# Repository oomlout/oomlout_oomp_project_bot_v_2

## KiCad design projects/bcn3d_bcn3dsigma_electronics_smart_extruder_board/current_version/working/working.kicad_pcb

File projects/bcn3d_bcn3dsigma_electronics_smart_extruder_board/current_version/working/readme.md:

# bcn3dsigma_electronics
 
## summary 
* id: bcn3d_bcn3dsigma_electronics_smart_extruder_board
* user: bcn3d
* name: bcn3dsigma_electronics
* board: smart_extruder_board
* repo: https://github.com/BCN3D/BCN3DSigma-Electronics

* src_file_repo_sch: 
* src_file_repo_sch_link: https://github.com/BCN3D/BCN3DSigma-Electronics/tree/master/
* full details link: https://github.com/oomlout/oomlout_oomp_project_bot_v_2/tree/main/projects/bcn3d_bcn3dsigma_electronics_smart_extruder_board/current_version/working  

## schematic  
  
[schematic (pdf)](working_schematic.pdf) 

## pcb  

[board (pdf)](working.pdf)  

## working_bom
| Id | Designator | Footprint | Quantity | Designation | Supplier and ref |  | None | 
| --- | --- | --- | --- | --- | --- | --- | --- | 
| 1 | @HOLE0,@HOLE1 |  | 2 |  |  |  | [''] | 
| 2 | C2,C1 | C0603K | 2 | 100n |  |  | [''] | 
| 3 | CFAN0,LFAN0,ENDSTOP0 | JST-2-SMD | 3 |  |  |  | [''] | 
| 4 | R8,R2 | R0603 | 2 | 10k |  |  | [''] | 
| 5 | R6,L1,R4 | R0603 | 3 | 1k |  |  | [''] | 
| 6 | R5 | R0603 | 1 | 200k |  |  | [''] | 
| 7 | U2 | SOT23-3 | 1 | LM3480IM4 |  |  | [''] | 
| 8 | R1 | R1210 | 1 | 100 |  |  | [''] | 
| 9 | U$1,U$2,U$3 | FIDUCIAL_1MM | 3 | FIDUCIAL |  |  | [''] | 
| 10 | U3 | MSOP8 | 1 | LM392MMSOP8 |  |  | [''] | 
| 11 | CN1 | JST_PA_04 | 1 |  |  |  | [''] | 
| 12 | D1 | POWERDI323 | 1 | PD3S160 |  |  | [''] | 
| 13 | Q2 | SOT323 | 1 | MOSFET-NSOT323 |  |  | [''] | 
| 14 | Q1 | SOT323-BEC | 1 | BC807W |  |  | [''] | 
| 15 | R3 | R0603 | 1 | 5k23 |  |  | [''] | 
| 16 | C3 | C0805 | 1 | 330n |  |  | [''] | 
| 17 | VERT_FFC1 | 68612014422 | 1 | 68612014422 |  |  | [''] | 
| 18 | R7 | R0603 | 1 | 22.6K |  |  | [''] | 
| 19 | GND0,THERM0,CFAN-0,UNK5V0,UNK24V0,CFAN+0 | B1,27 | 6 | TPB1,27 |  |  | [''] | 
| 20 | U$5 | OSHW-LOGO-S | 1 |  |  |  | [''] | 
| 21 | U$6 | FCIM_LOGO | 1 |  |  |  | [''] | 

## bom_schematic
| Ref | Qnty | Value | Cmp name | Footprint | Description | Vendor | DNP | 
| --- | --- | --- | --- | --- | --- | --- | --- | 
| C1, C2 | 2 | 100n | C-EUC0603K | working:C0603K |  |  |  | 
| C3 | 1 | 330n | C-EUC0805 | working:C0805 |  |  |  | 
| CFAN0 | 1 | JST_2MM_MALE | JST_2MM_MALE | working:JST-2-SMD |  |  |  | 
| CFAN+0 | 1 | TPB1,27 | TPB1,27 | working:B1,27 |  |  |  | 
| CFAN-0 | 1 | TPB1,27 | TPB1,27 | working:B1,27 |  |  |  | 
| CN1 | 1 | JST_4PINPA | JST_4PINPA | working:JST_PA_04 |  |  |  | 
| D1 | 1 | PD3S160 | PD3S160 | working:POWERDI323 |  |  |  | 
| ENDSTOP0 | 1 | JST_2MM_MALE | JST_2MM_MALE | working:JST-2-SMD |  |  |  | 
| GND0 | 1 | TPB1,27 | TPB1,27 | working:B1,27 |  |  |  | 
| L1 | 1 | 1k | R-US_R0603 | working:R0603 |  |  |  | 
| LFAN0 | 1 | JST_2MM_MALE | JST_2MM_MALE | working:JST-2-SMD |  |  |  | 
| Q1 | 1 | BC807W | BC807W | working:SOT323-BEC |  |  |  | 
| Q2 | 1 | MOSFET-NSOT323 | MOSFET-NSOT323 | working:SOT323 |  |  |  | 
| R1 | 1 | 100 | R-US_R1210 | working:R1210 |  |  |  | 
| R2, R8 | 2 | 10k | R-US_R0603 | working:R0603 |  |  |  | 
| R3 | 1 | 5k23 | R-US_R0603 | working:R0603 |  |  |  | 
| R4, R6 | 2 | 1k | R-US_R0603 | working:R0603 |  |  |  | 
| R5 | 1 | 200k | R-US_R0603 | working:R0603 |  |  |  | 
| R7 | 1 | 22.6K | R-US_R0603 | working:R0603 |  |  |  | 
| THERM0 | 1 | TPB1,27 | TPB1,27 | working:B1,27 |  |  |  | 
| U2 | 1 | LM3480IM4 | LM3480IM4 | working:SOT23-3 |  |  |  | 
| U3 | 1 | LM392MMSOP8 | LM392MMSOP8 | working:MSOP8 |  |  |  | 
| U$1, U$2, U$3 | 3 | FIDUCIAL | FIDUCIAL | working:FIDUCIAL_1MM |  |  |  | 
| UNK5V0 | 1 | TPB1,27 | TPB1,27 | working:B1,27 |  |  |  | 
| UNK24V0 | 1 | TPB1,27 | TPB1,27 | working:B1,27 |  |  |  | 
| VERT_FFC1 | 1 | 68612014422 | 68612014422 | working:68612014422 |  |  |  |

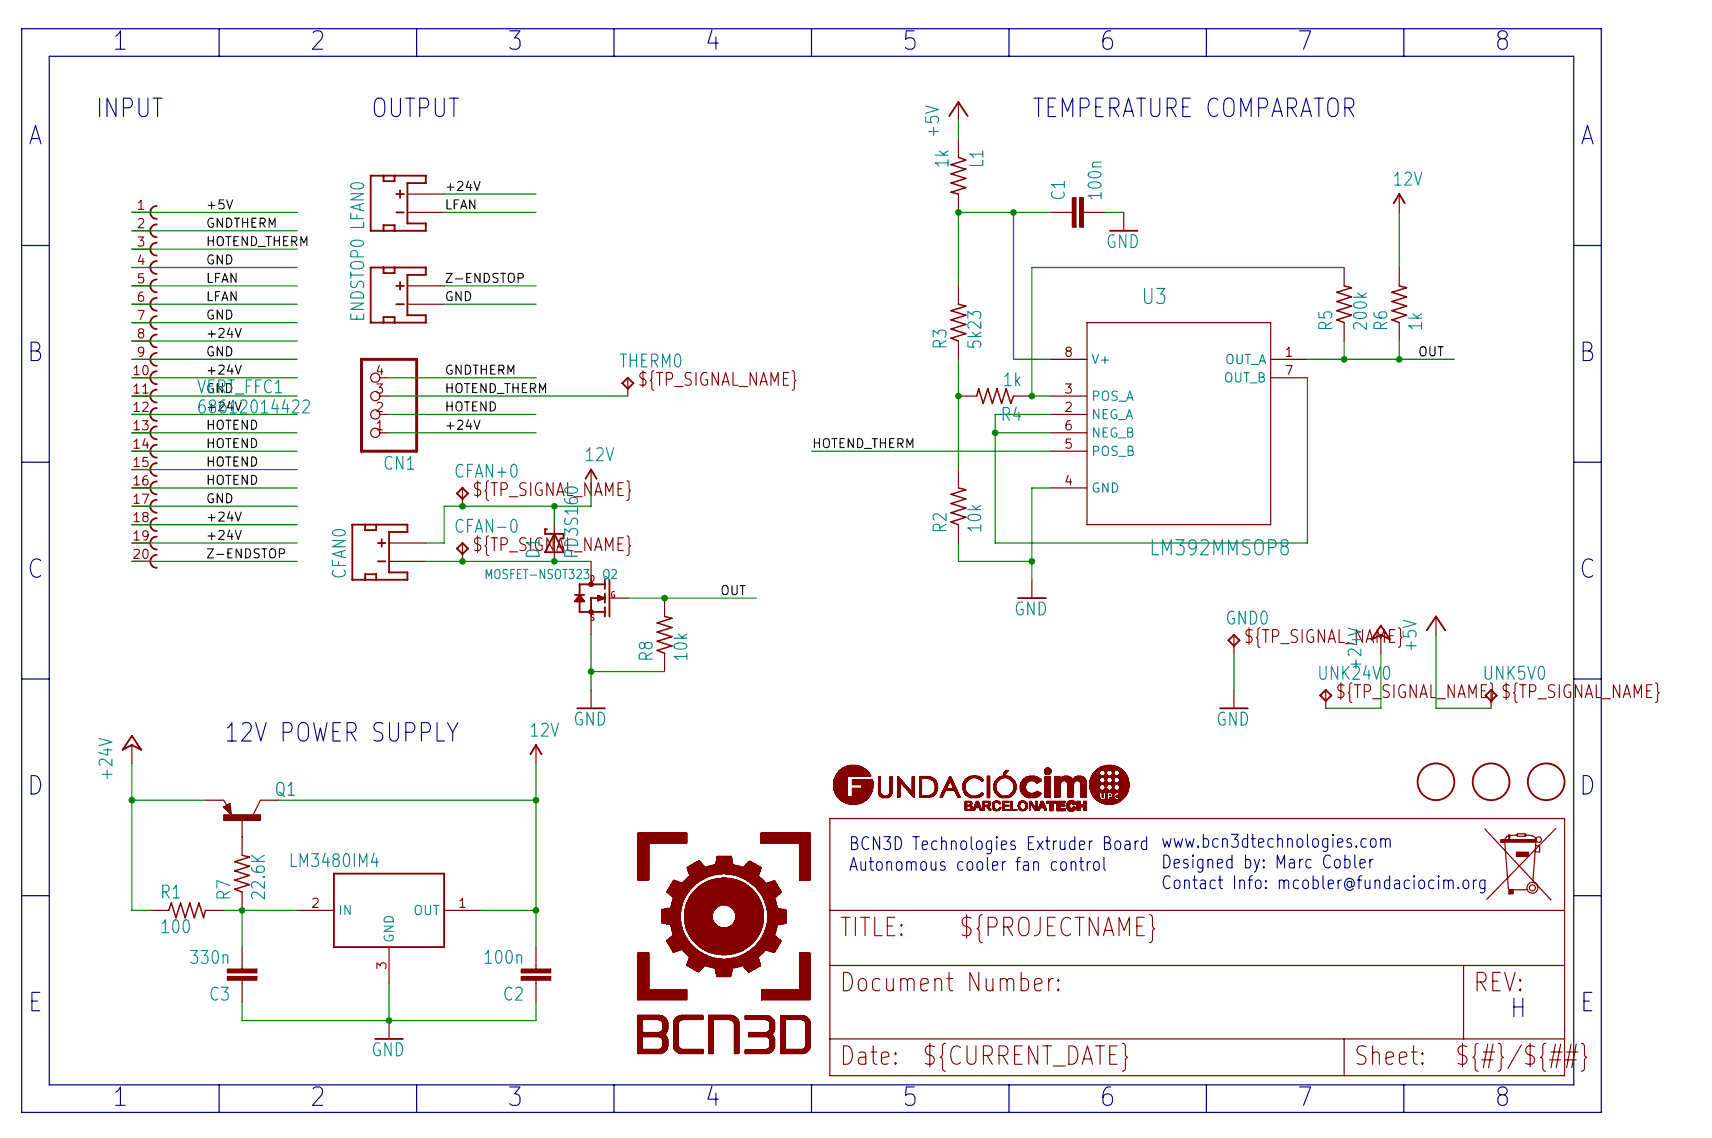
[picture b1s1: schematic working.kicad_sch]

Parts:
C1, C2: 100n; C0603K; MPN 06035C104KAT2A
C3: 330n; C0805; MPN GRM219R71H334KA88D
CFAN0: JST_2MM_MALE; JST-2-SMD; MPN S2B-PH-SM4-TB(LF)(SN)
CFAN+0: TPB1,27; B1,27
CFAN-0: TPB1,27; B1,27
CN1: JST_4PINPA; JST_PA_04; MPN SM04B-PASS-TBT(LF)(SN)
D1: PD3S160; POWERDI323; MPN PD3S160-7
ENDSTOP0: JST_2MM_MALE; JST-2-SMD; MPN S2B-PH-SM4-TB(LF)(SN)
GND0: TPB1,27; B1,27
L1: 1k; R0603; MPN MCMR06X1001FTL
LFAN0: JST_2MM_MALE; JST-2-SMD; MPN S2B-PH-SM4-TB(LF)(SN)
Q1: BC807W; SOT323-BEC; MPN BC807W,115
Q2: MOSFET-NSOT323; SOT323; MPN PMF370XN,115
R1: 100; R1210; MPN MC0603SAF330JT5E
R2, R8: 10k; R0603; MPN MCMR06X1002FTL
R3: 5k23; R0603; MPN ERJ3EKF5231V
R4, R6: 1k; R0603; MPN MCMR06X1001FTL
R5: 200k; R0603; MPN ERJ3EKF2003V
R7: 22.6K; R0603; MPN MC0603SAF330JT5E
THERM0: TPB1,27; B1,27
U2: LM3480IM4; SOT23-3; MPN LM3480IM3-12/NOPB
U3: LM392MMSOP8; MSOP8
U$1, U$2, U$3: FIDUCIAL; FIDUCIAL_1MM
UNK5V0, UNK24V0: TPB1,27; B1,27
VERT_FFC1: 68612014422

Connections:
12V: C2.2, CFAN0.2 (+), CFAN+0.TP, D1.C, Q1.3 (C), R6.2, U2.1 (OUT)
+5V: L1.1, UNK5V0.TP, VERT_FFC1.1
+24V: CN1.1, LFAN0.2 (+), Q1.2 (E), R1.1, UNK24V0.TP, VERT_FFC1.8, VERT_FFC1.10, VERT_FFC1.12, VERT_FFC1.18, VERT_FFC1.19
DRAIN: CFAN0.1 (-), CFAN-0.TP, D1.A, Q2.3 (D)
GND: C1.2, C2.1, C3.1, ENDSTOP0.1 (-), GND0.TP, Q2.2 (S), R2.1, R8.1, U2.3 (GND), U3.4 (GND), VERT_FFC1.4, VERT_FFC1.7, VERT_FFC1.9, VERT_FFC1.11, VERT_FFC1.17
GNDTHERM: CN1.4, VERT_FFC1.2
HOTEND: CN1.2, VERT_FFC1.13, VERT_FFC1.14, VERT_FFC1.15, VERT_FFC1.16
HOTEND_THERM: CN1.3, THERM0.TP, U3.5 (POS_B), VERT_FFC1.3
IN: C3.2, R1.2, R7.1, U2.2 (IN)
LFAN: LFAN0.1 (-), VERT_FFC1.5, VERT_FFC1.6
unnamed: Q1.1 (B), R7.2
unnamed: C1.1, L1.2, R3.2, U3.8 (V+)
unnamed: U3.2 (NEG_A), U3.6 (NEG_B), U3.7 (OUT_B)
unnamed: R2.2, R3.1, R4.2
unnamed: R4.1, R5.2, U3.3 (POS_A)
OUT: Q2.1 (G), R5.1, R6.1, R8.2, U3.1 (OUT_A)
Z-ENDSTOP: ENDSTOP0.2 (+), VERT_FFC1.20

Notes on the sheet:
BCN3D Technologies Extruder Board Autonomous cooler fan control
12V POWER SUPPLY
INPUT
www.bcn3dtechnologies.com Designed by: Marc Cobler Contact Info: mcobler@fundaciocim.org
OUTPUT
TEMPERATURE COMPARATOR

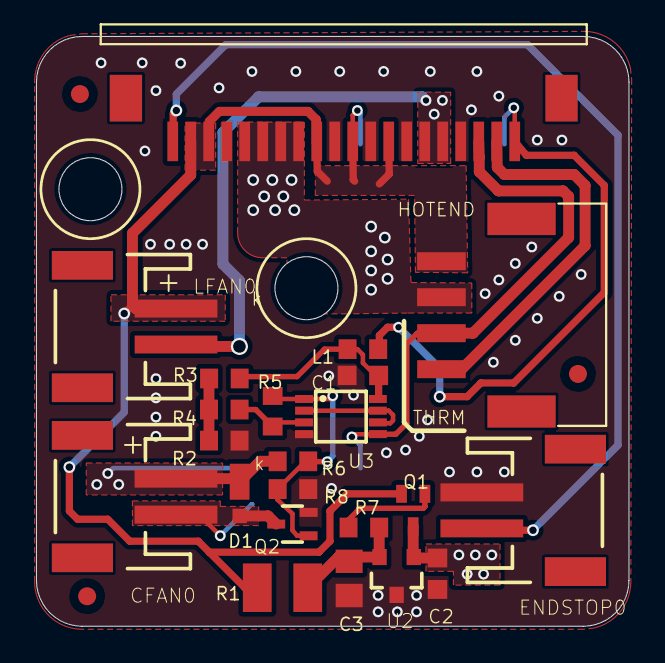
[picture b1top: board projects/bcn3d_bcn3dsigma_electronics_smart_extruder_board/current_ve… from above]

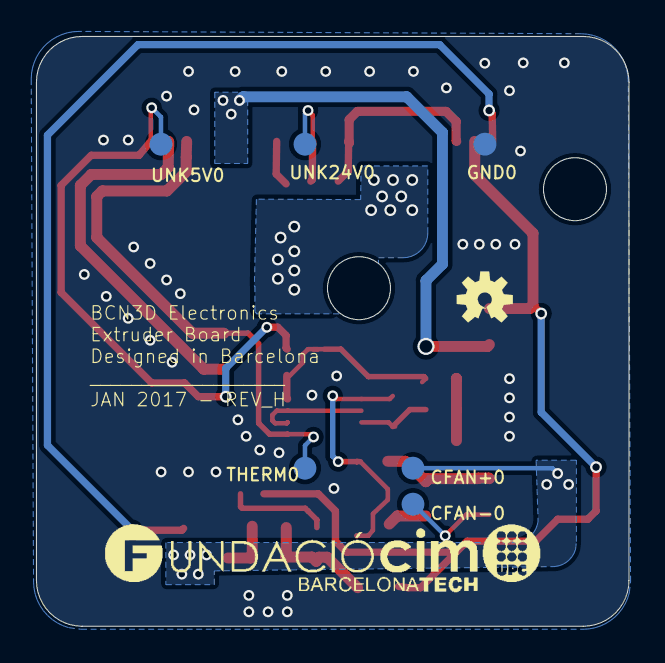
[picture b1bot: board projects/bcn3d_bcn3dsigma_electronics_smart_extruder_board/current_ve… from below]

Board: 2 copper layers, 32.9 x 32.8 mm, 35 parts (8 on the bottom side), 17 nets.

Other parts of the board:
@HOLE0, @HOLE1: (no value)
U$5: OSHW-LOGO-S
U$6: FCIM_LOGO

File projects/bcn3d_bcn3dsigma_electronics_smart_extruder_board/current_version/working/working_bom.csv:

"Id";"Designator";"Footprint";"Quantity";"Designation";"Supplier and ref";
1;"@HOLE0,@HOLE1";"";2;"";;;
2;"C2,C1";"C0603K";2;"100n";;;
3;"CFAN0,LFAN0,ENDSTOP0";"JST-2-SMD";3;"";;;
4;"R8,R2";"R0603";2;"10k";;;
5;"R6,L1,R4";"R0603";3;"1k";;;
6;"R5";"R0603";1;"200k";;;
7;"U2";"SOT23-3";1;"LM3480IM4";;;
8;"R1";"R1210";1;"100";;;
9;"U$1,U$2,U$3";"FIDUCIAL_1MM";3;"FIDUCIAL";;;
10;"U3";"MSOP8";1;"LM392MMSOP8";;;
11;"CN1";"JST_PA_04";1;"";;;
12;"D1";"POWERDI323";1;"PD3S160";;;
13;"Q2";"SOT323";1;"MOSFET-NSOT323";;;
14;"Q1";"SOT323-BEC";1;"BC807W";;;
15;"R3";"R0603";1;"5k23";;;
16;"C3";"C0805";1;"330n";;;
17;"VERT_FFC1";"68612014422";1;"68612014422";;;
18;"R7";"R0603";1;"22.6K";;;
19;"GND0,THERM0,CFAN-0,UNK5V0,UNK24V0,CFAN+0";"B1,27";6;"TPB1,27";;;
20;"U$5";"OSHW-LOGO-S";1;"";;;
21;"U$6";"FCIM_LOGO";1;"";;;

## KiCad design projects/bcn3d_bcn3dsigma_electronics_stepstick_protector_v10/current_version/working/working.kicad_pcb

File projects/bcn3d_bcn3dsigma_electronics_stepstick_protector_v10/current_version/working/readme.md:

# bcn3dsigma_electronics
 
## summary 
* id: bcn3d_bcn3dsigma_electronics_stepstick_protector_v10
* user: bcn3d
* name: bcn3dsigma_electronics
* board: stepstick_protector_v10
* repo: https://github.com/BCN3D/BCN3DSigma-Electronics

* src_file_repo_sch: 
* src_file_repo_sch_link: https://github.com/BCN3D/BCN3DSigma-Electronics/tree/master/
* full details link: https://github.com/oomlout/oomlout_oomp_project_bot_v_2/tree/main/projects/bcn3d_bcn3dsigma_electronics_stepstick_protector_v10/current_version/working  

## schematic  
  
[schematic (pdf)](working_schematic.pdf) 

## pcb  

[board (pdf)](working.pdf)  

## working_bom
| Id | Designator | Footprint | Quantity | Designation | Supplier and ref |  | None | 
| --- | --- | --- | --- | --- | --- | --- | --- | 
| 1 | C3 | C0402 | 1 | 470n/10V |  |  | [''] | 
| 2 | X1,X2 | PASSER_07MM | 2 | PASSER-07 |  |  | [''] | 
| 3 | C1,C7,C2,C6 | C0402 | 4 | 100n/50V |  |  | [''] | 
| 4 | C5 | C0402 | 1 | 22n/50V |  |  | [''] | 
| 5 | R2,R4 | M0805 | 2 | R0805/0R11 |  |  | [''] | 
| 6 | IC1 | QFN36-PAD | 1 | TMC2100-LA |  |  | [''] | 
| 7 | JP4,JP3,JP5 | 1X01 | 3 |  |  |  | [''] | 
| 8 | CFG5,CFG4 | JUMPER3-0201 | 2 | JUMPER3-0201 |  |  | [''] | 
| 9 | C8 | C0603 | 1 | 1u/50V |  |  | [''] | 
| 10 | R5 | C0402 | 1 | 20k |  |  | [''] | 
| 11 | C4 | C0402 | 1 | 4u7/10V |  |  | [''] | 
| 12 | JP1,JP2 | 1X08-S | 2 |  |  |  | [''] | 
| 13 | R1 | C0402 | 1 | 2R2 |  |  | [''] | 
| 14 | SPI0 | JUMPER2-0402_NC | 1 | JUMPER2-0402-NC |  |  | [''] | 
| 15 | R6 | POT_EVM3R | 1 | 20k |  |  | [''] | 
| 16 | LOGO2 | SPARK_TPLACE_M | 1 | LOGO-S_PLACE_M |  |  | [''] | 
| 17 | LOGO1 | OSHW_6X70 | 1 | OSHW_LOGOX0070 |  |  | [''] | 

## bom_schematic
| Ref | Qnty | Value | Cmp name | Footprint | Description | Vendor | DNP | 
| --- | --- | --- | --- | --- | --- | --- | --- | 
| C1, C2, C6, C7 | 4 | 100n/50V | CAPACITOR-0402 | working:C0402 |  |  |  | 
| C3 | 1 | 470n/10V | CAPACITOR-0402 | working:C0402 |  |  |  | 
| C4 | 1 | 4u7/10V | CAPACITOR-0402 | working:C0402 |  |  |  | 
| C5 | 1 | 22n/50V | CAPACITOR-0402 | working:C0402 |  |  |  | 
| C8 | 1 | 1u/50V | C-EUC0603 | working:C0603 |  |  |  | 
| CFG4, CFG5 | 2 | JUMPER3-0201 | JUMPER3-0201 | working:JUMPER3-0201 |  |  |  | 
| IC1 | 1 | TMC2100-LA | TMC2100-LA | working:QFN36-PAD |  |  |  | 
| JP1, JP2 | 2 | PINHD-1X08_2.54-S | PINHD-1X08_2.54-S | working:1X08-S |  |  |  | 
| JP3, JP4, JP5 | 3 | PINHD-1X1 | PINHD-1X1 | working:1X01 |  |  |  | 
| LOGO1 | 1 | OSHW_LOGOX0070 | OSHW_LOGOX0070 | working:OSHW_6X70 |  |  |  | 
| LOGO2 | 1 | LOGO-S_PLACE_M | LOGO-S_PLACE_M | working:SPARK_TPLACE_M |  |  |  | 
| R1 | 1 | 2R2 | RESISTOR-0402 | working:C0402 |  |  |  | 
| R2, R4 | 2 | R0805/0R11 | R-EU_M0805 | working:M0805 |  |  |  | 
| R5 | 1 | 20k | RESISTOR-0402 | working:C0402 |  |  |  | 
| R6 | 1 | 20k | POTEVM3R | working:POT_EVM3R |  |  |  | 
| SPI0 | 1 | JUMPER2-0402-NC | JUMPER2-0402-NC | working:JUMPER2-0402_NC |  |  |  | 
| X1, X2 | 2 | PASSER-07 | PASSER-07 | working:PASSER_07MM |  |  |  |

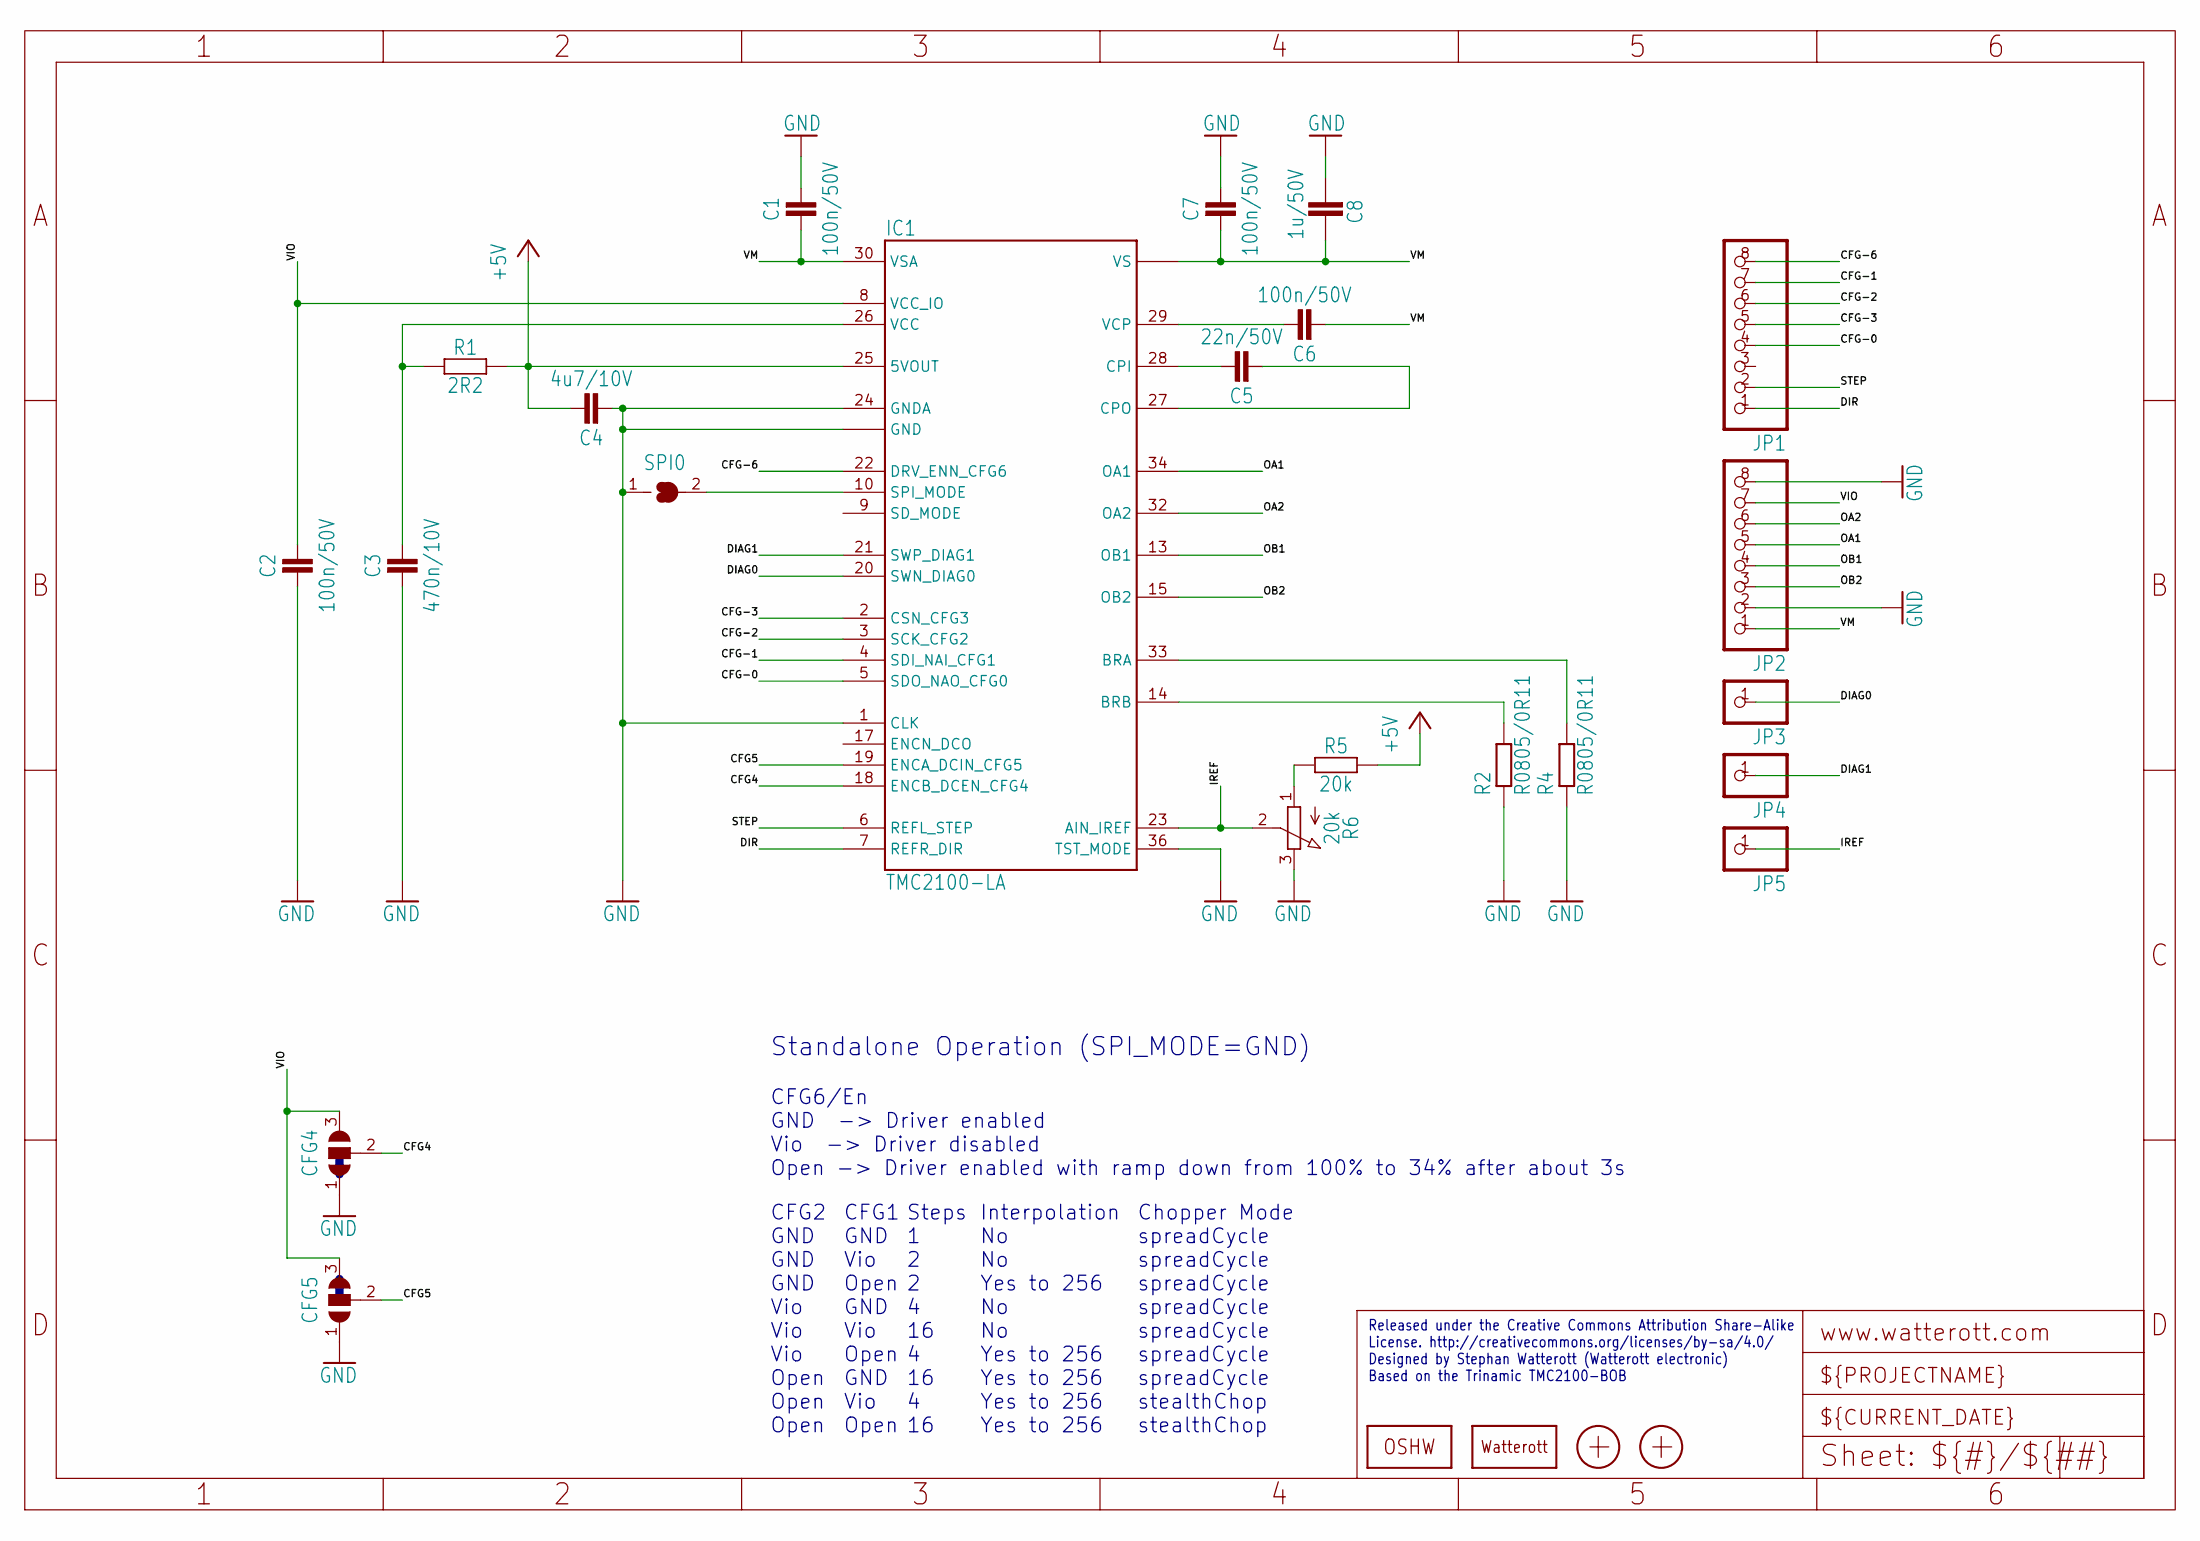
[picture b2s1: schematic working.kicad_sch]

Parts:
C1, C2, C6, C7: 100n/50V; C0402
C3: 470n/10V; C0402
C4: 4u7/10V; C0402
C5: 22n/50V; C0402
C8: 1u/50V; C0603
CFG4, CFG5: JUMPER3-0201
IC1: TMC2100-LA; QFN36-PAD
JP1, JP2: PINHD-1X08_2.54-S; 1X08-S
JP3, JP4, JP5: PINHD-1X1; 1X01
LOGO1: OSHW_LOGOX0070; OSHW_6X70
LOGO2: LOGO-S_PLACE_M; SPARK_TPLACE_M
R1: 2R2; C0402
R2, R4: R0805/0R11; M0805
R5: 20k; C0402
R6: 20k; POT_EVM3R
SPI0: JUMPER2-0402-NC; JUMPER2-0402_NC
X1, X2: PASSER-07; PASSER_07MM

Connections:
+5V: C4.2, IC1.25 (5VOUT), R1.2, R5.2
BRA: IC1.33 (BRA), R4.2
BRB: IC1.14 (BRB), R2.2
CFG4: CFG4.2, IC1.18 (ENCB_DCEN_CFG4)
CFG5: CFG5.2, IC1.19 (ENCA_DCIN_CFG5)
CFG-0: IC1.5 (SDO_NAO_CFG0), JP1.4
CFG-1: IC1.4 (SDI_NAI_CFG1), JP1.7
CFG-2: IC1.3 (SCK_CFG2), JP1.6
CFG-3: IC1.2 (CSN_CFG3), JP1.5
CFG-6: IC1.22 (DRV_ENN_CFG6), JP1.8
CPI: C5.2, IC1.28 (CPI)
CPO: C5.1, IC1.27 (CPO)
DIAG0: IC1.20 (SWN_DIAG0), JP3.1
DIAG1: IC1.21 (SWP_DIAG1), JP4.1
DIR: IC1.7 (REFR_DIR), JP1.1
GND: C1.2, C2.1, C3.1, C4.1, C7.2, C8.2, CFG4.1, CFG5.1, IC1.1 (CLK), IC1.11 (GND), IC1.12 (GND), IC1.24 (GNDA), IC1.35 (GND), IC1.36 (TST_MODE), IC1.TP (GND), JP2.2, JP2.8, R2.1, R4.1, R6.3 (E), SPI0.1
IREF: IC1.23 (AIN_IREF), JP5.1, R6.2 (S)
unnamed: IC1.10 (SPI_MODE), SPI0.2
OA1: IC1.34 (OA1), JP2.5
OA2: IC1.32 (OA2), JP2.6
OB1: IC1.13 (OB1), JP2.4
OB2: IC1.15 (OB2), JP2.3
STEP: IC1.6 (REFL_STEP), JP1.2
VCC: C3.2, IC1.26 (VCC), R1.1
VCP: C6.2, IC1.29 (VCP)
VIO: C2.2, CFG4.3, CFG5.3, IC1.8 (VCC_IO), JP2.7
VM: C1.1, C6.1, C7.1, C8.1, IC1.16 (VS), IC1.30 (VSA), IC1.31 (VS), JP2.1
VREF1: R5.1, R6.1 (A)

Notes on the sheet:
Standalone Operation (SPI_MODE=GND)
Released under the Creative Commons Attribution Share-Alike License. http://creativecommons.org/licenses/by-sa/4.0/ Designed by Stephan Watterott (Watterott electronic) Based on the Trinamic TMC2100-BOB
Interpolation No No Yes to 256 No No Yes to 256 Yes to 256 Yes to 256 Yes to 256
Steps 1 2 2 4 16 4 16 4 16
CFG6/En GND -> Driver enabled Vio -> Driver disabled Open -> Driver enabled with ramp down from 100% to 34% after about 3s
Chopper Mode spreadCycle spreadCycle spreadCycle spreadCycle spreadCycle spreadCycle spreadCycle stealthChop stealthChop
CFG1 GND Vio Open GND Vio Open GND Vio Open
CFG2 GND GND GND Vio Vio Vio Open Open Open

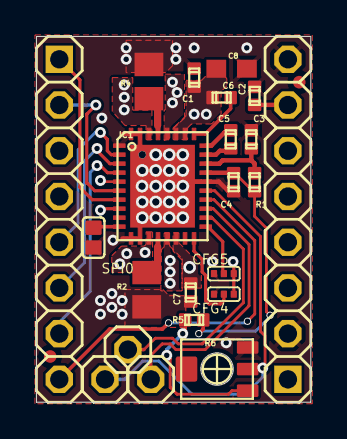
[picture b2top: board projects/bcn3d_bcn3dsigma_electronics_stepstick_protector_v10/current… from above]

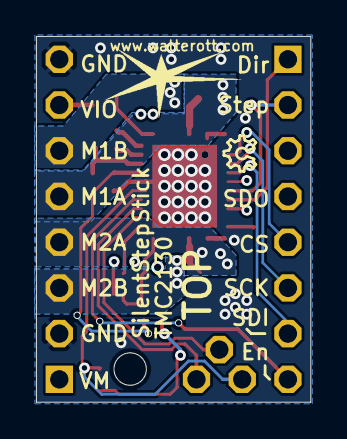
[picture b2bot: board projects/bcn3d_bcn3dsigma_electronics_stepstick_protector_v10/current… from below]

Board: 4 copper layers, 15.2 x 20.3 mm, 26 parts (2 on the bottom side), 28 nets.

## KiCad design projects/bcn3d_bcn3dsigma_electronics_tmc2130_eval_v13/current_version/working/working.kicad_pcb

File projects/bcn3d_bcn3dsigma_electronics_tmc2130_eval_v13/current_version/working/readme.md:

# bcn3dsigma_electronics
 
## summary 
* id: bcn3d_bcn3dsigma_electronics_tmc2130_eval_v13
* user: bcn3d
* name: bcn3dsigma_electronics
* board: tmc2130_eval_v13
* repo: https://github.com/BCN3D/BCN3DSigma-Electronics

* src_file_repo_sch: 
* src_file_repo_sch_link: https://github.com/BCN3D/BCN3DSigma-Electronics/tree/master/
* full details link: https://github.com/oomlout/oomlout_oomp_project_bot_v_2/tree/main/projects/bcn3d_bcn3dsigma_electronics_tmc2130_eval_v13/current_version/working  

## schematic  
  
[schematic (pdf)](working_schematic.pdf) 

## pcb  

[board (pdf)](working.pdf)  

## working_bom
| Id | Designator | Footprint | Quantity | Designation | Supplier and ref |  | None | 
| --- | --- | --- | --- | --- | --- | --- | --- | 
| 1 | PROBE_GND3,RSENSE_B0,PROBE_GND0,PROBE_GND2,PROBE_GND1,AIN_REF0,RSENSE_A0 | 1PIN_1ROW_THT | 7 | NOT ASSEMBLED |  |  | [''] | 
| 2 | TMC2130 | QFN36 | 1 | TMC2130_QFN36 |  |  | [''] | 
| 3 | JMP2 | EXTRA_TERMINAL | 1 | JUMPER_2.54MM BLACK ON X1 |  |  | [''] | 
| 4 | C7,C15,C5,C10 | C0603 | 4 | C0603/100nF/50V |  |  | [''] | 
| 5 | R11 | RCL_0603 | 1 | 15k/0603/1% |  |  | [''] | 
| 6 | INTERFACE_TO_UC/MC0 | FEMALE_HEADER_SMD_254_44_PIN_SHORTPADS_HOLES | 1 |  |  |  | [''] | 
| 7 | R10 | RCL_0603 | 1 | 10k/0603/1% |  |  | [''] | 
| 8 | R15,R14 | 0603 | 2 | 0603/1k/1% |  |  | [''] | 
| 9 | X1,REF2,X2 | 3PIN_1ROW_2,54_THT | 3 | MALE HEADER 2.54 |  |  | [''] | 
| 10 | TERM2 | EXTRA_TERMINAL | 1 | AKL182_04_POL_TERMINAL |  |  | [''] | 
| 11 | C12,C13 | C_POL_RAD_THT_5X10X12.5 | 2 | EEUFR1J151 150uF/63V/0R045 |  |  | [''] | 
| 12 | C1,C2 | RCL_0603 | 2 | 0603/4.7ÂµF/10V |  |  | [''] | 
| 13 | MOTOR1 | AKL169_04_POL | 1 | AKL182_04_POL_HEADER |  |  | [''] | 
| 14 | PWR0 | AKL349_02_POL | 1 | AKL_349_02_POL_HEADER |  |  | [''] | 
| 15 | IC2 | SOT23-5 | 1 | LP2985AIM5-3.3 |  |  | [''] | 
| 16 | D3,D4 | SOT23 | 2 | BAT54S |  |  | [''] | 
| 17 | JMP1 | EXTRA_TERMINAL | 1 | JUMPER_2.54MM BLACK ON X2 |  |  | [''] | 
| 18 | C8 | C0603 | 1 | C0603/22nF/50V |  |  | [''] | 
| 19 | D1 | SMB | 1 | SMBJ43A |  |  | [''] | 
| 20 | R9 | R0603 | 1 | 0603/0R |  |  | [''] | 
| 21 | R7,R5 | R1206 | 2 | R1206,0R22/0.5W |  |  | [''] | 
| 22 | R_ID0 | RCL_0603 | 1 | R_ID/1% |  |  | [''] | 
| 23 | U$1 | TMC_EVAL_RIGHT_BAR | 1 |  |  |  | [''] | 
| 24 | R_SPI0,R_SD0 | RCL_0603 | 2 | NOT_ASSEMBLED |  |  | [''] | 
| 25 | R13,R12 | 0603 | 2 | 0603/10k/1% |  |  | [''] | 
| 26 | C3 | RCL_0603 | 1 | 0603/10nF/10V |  |  | [''] | 
| 27 | R17 | RCL_0603 | 1 | 4k7/0603/1% |  |  | [''] | 
| 28 | TERM1 | EXTRA_TERMINAL | 1 | AKL_330_2_POL_TERMINAL |  |  | [''] | 
| 29 | C_ID0 | RCL_0603 | 1 | C_ID/10V/1% |  |  | [''] | 
| 30 | C9 | C0603 | 1 | C0603/470nF/16V |  |  | [''] | 
| 31 | R1 | RCL_0603 | 1 | 0603/10k/1% |  |  | [''] | 
| 32 | R2 | RCL_0603 | 1 | 10K |  |  | [''] | 
| 33 | R8 | R0603 | 1 | NOT ASSEMBLED |  |  | [''] | 
| 34 | C6 | C0603 | 1 | C0603/4Âµ7/16V |  |  | [''] | 
| 35 | IC1 | SN74LVC1G123DCTR | 1 | SN74LVC1G123DCTR |  |  | [''] | 
| 36 | R6 | R0603 | 1 | 0603/2R2/1% |  |  | [''] | 
| 37 | C11 | C1210 | 1 | 1210/4.7uF/100V |  |  | [''] | 
| 38 | C14 | C0805 | 1 | 0805/4Âµ7/50V |  |  | [''] | 
| 39 | TEST_POINT14,TEST_POINT7,TEST_POINT3,TEST_POINT5,TEST_POINT2,TEST_POINT1,TEST_POINT6,TEST_POINT11,TEST_POINT9,TEST_POINT10,TEST_POINT4,TEST_POINT8,TEST_POINT12,TEST_POINT13 | PAD_R1.2 | 14 | NOT ASSEMBLED |  |  | [''] | 
| 40 | U$3 | TMC_EVAL_BACK_NO_DOCU | 1 |  |  |  | [''] | 

## bom_schematic
| Ref | Qnty | Value | Cmp name | Footprint | Description | Vendor | DNP | 
| --- | --- | --- | --- | --- | --- | --- | --- | 
| AIN_REF0 | 1 | 1PIN_1ROW | 1PIN_1ROW | working:1PIN_1ROW_THT |  |  |  | 
| C1, C2 | 2 | 0603/4.7ÂµF/10V | RCL_C/0603 | working:RCL_0603 |  |  |  | 
| C3 | 1 | 0603/10nF/10V | RCL_C/0603 | working:RCL_0603 |  |  |  | 
| C5, C7, C10, C15 | 4 | C0603/100nF/50V | C-EUC0603 | working:C0603 |  |  |  | 
| C6 | 1 | C0603/4Âµ7/16V | C-EUC0603 | working:C0603 |  |  |  | 
| C8 | 1 | C0603/22nF/50V | C-EUC0603 | working:C0603 |  |  |  | 
| C9 | 1 | C0603/470nF/16V | C-EUC0603 | working:C0603 |  |  |  | 
| C11 | 1 | 1210/4.7uF/100V | C-EUC1210 | working:C1210 |  |  |  | 
| C12, C13 | 2 | EEUFR1J151 150uF/63V/0R045 | C_POL | working:C_POL_RAD_THT_5X10X12.5 |  |  |  | 
| C14 | 1 | 0805/4Âµ7/50V | C-EUC0805 | working:C0805 |  |  |  | 
| C_ID0 | 1 | C_ID/10V/1% | RCL_C/0603 | working:RCL_0603 |  |  |  | 
| D1 | 1 | SMBJ43A | SMBJ | working:SMB |  |  |  | 
| D3, D4 | 2 | BAT54S | BAT54S | working:SOT23 |  |  |  | 
| IC1 | 1 | SN74LVC1G123DCTR | SN74LVC1G123DCTR | working:SN74LVC1G123DCTR |  |  |  | 
| IC2 | 1 | LP2985AIM5-3.3 | LP2985AIM5-3.3 | working:SOT23-5 |  |  |  | 
| INTERFACE_TO_UC/MC0 | 1 | FEMALE_HEADER_SMD_2.54_44_PINSHORTPADS_HOLES | FEMALE_HEADER_SMD_2.54_44_PINSHORTPADS_HOLES | working:FEMALE_HEADER_SMD_254_44_PIN_SHORTPADS_HOLES |  |  |  | 
| JMP1, JMP2 | 2 | JUMPER_2.54MM | JUMPER_2.54MM | working:EXTRA_TERMINAL |  |  |  | 
| MOTOR1 | 1 | AKL182_04_POL_HEADER | AKL182_04_POL_HEADER | working:AKL169_04_POL |  |  |  | 
| PROBE_GND0, PROBE_GND1, PROBE_GND2, PROBE_GND3 | 4 | 1PIN_1ROW | 1PIN_1ROW | working:1PIN_1ROW_THT |  |  |  | 
| PWR0 | 1 | AKL_349_02_POL_HEADER | AKL_349_02_POL_HEADER | working:AKL349_02_POL |  |  |  | 
| R1 | 1 | 0603/10k/1% | RCL_R/0603 | working:RCL_0603 |  |  |  | 
| R2 | 1 | 10K | RCL_R/0603 | working:RCL_0603 |  |  |  | 
| R5, R7 | 2 | R1206,0R22/0.5W | R-EU_R1206 | working:R1206 |  |  |  | 
| R6 | 1 | 0603/2R2/1% | R-EU_R0603 | working:R0603 |  |  |  | 
| R8 | 1 | NOT ASSEMBLED | R-EU_R0603 | working:R0603 |  |  |  | 
| R9 | 1 | 0603/0R | R-EU_R0603 | working:R0603 |  |  |  | 
| R10 | 1 | 10k/0603/1% | RCL_R/0603 | working:RCL_0603 |  |  |  | 
| R11 | 1 | 15k/0603/1% | RCL_R/0603 | working:RCL_0603 |  |  |  | 
| R12, R13 | 2 | 0603/10k/1% | R/0603 | working:0603 |  |  |  | 
| R14, R15 | 2 | 0603/1k/1% | R/0603 | working:0603 |  |  |  | 
| R17 | 1 | 4k7/0603/1% | RCL_R/0603 | working:RCL_0603 |  |  |  | 
| R_ID0 | 1 | R_ID/1% | RCL_R/0603 | working:RCL_0603 |  |  |  | 
| R_SD0 | 1 | NOT_ASSEMBLED | RCL_R/0603 | working:RCL_0603 |  |  |  | 
| R_SPI0 | 1 | NOT_ASSEMBLED | RCL_R/0603 | working:RCL_0603 |  |  |  | 
| REF2 | 1 | 3PIN_1ROWTHT | 3PIN_1ROWTHT | working:3PIN_1ROW_2,54_THT |  |  |  | 
| RSENSE_A0 | 1 | 1PIN_1ROW | 1PIN_1ROW | working:1PIN_1ROW_THT |  |  |  | 
| RSENSE_B0 | 1 | 1PIN_1ROW | 1PIN_1ROW | working:1PIN_1ROW_THT |  |  |  | 
| TERM1 | 1 | AKL_330_2_POL_TERMINAL | AKL_330_2_POL_TERMINAL | working:EXTRA_TERMINAL |  |  |  | 
| TERM2 | 1 | AKL182_04_POL_TERMINAL | AKL182_04_POL_TERMINAL | working:EXTRA_TERMINAL |  |  |  | 
| TEST_POINT1, TEST_POINT2, TEST_POINT3, TEST_POINT4, TEST_POINT5, TEST_POINT6, TEST_POINT7, TEST_POINT8, TEST_POINT9, TEST_POINT10, TEST_POINT11, TEST_POINT12, TEST_POINT13, TEST_POINT14 | 14 | PAD_ROUND | PAD_ROUND | working:PAD_R1.2 |  |  |  | 
| TMC2130 | 1 | TMC2130_QFN36 | TMC2130_QFN36 | working:QFN36 |  |  |  | 
| X1, X2 | 2 | 3PIN_1ROWTHT | 3PIN_1ROWTHT | working:3PIN_1ROW_2,54_THT |  |  |  |

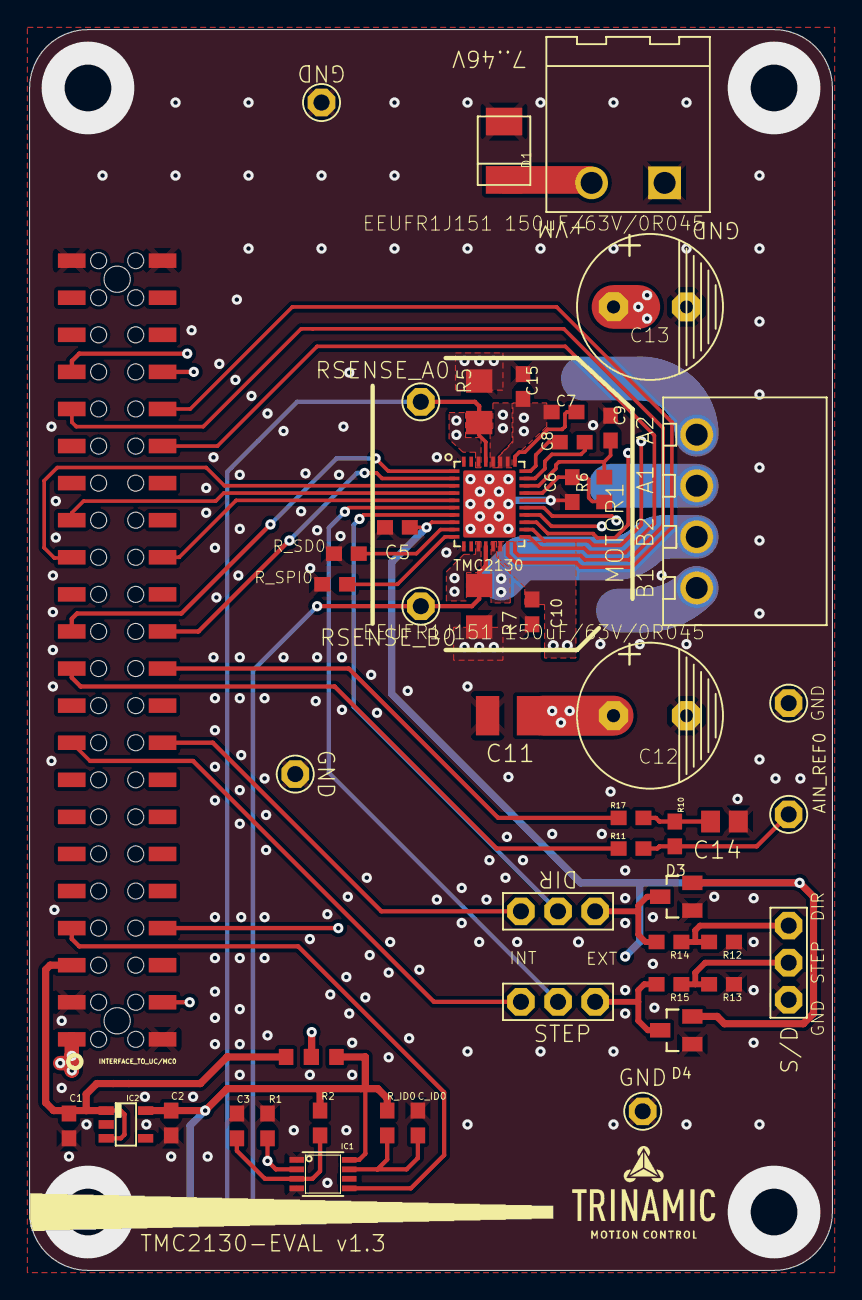
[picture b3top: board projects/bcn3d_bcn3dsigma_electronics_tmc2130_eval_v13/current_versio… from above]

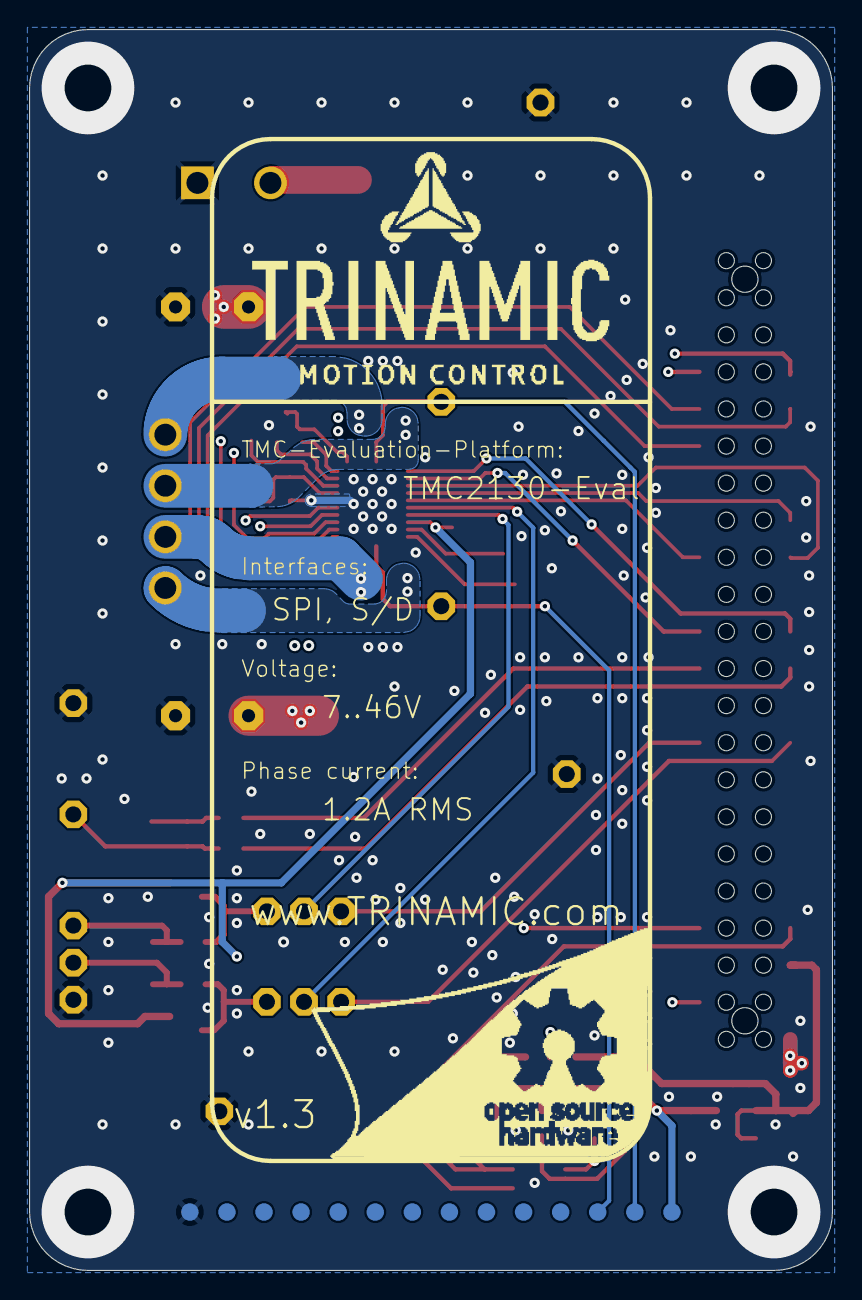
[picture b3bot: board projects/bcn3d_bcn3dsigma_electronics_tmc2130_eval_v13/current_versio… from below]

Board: 4 copper layers, 55.0 x 85.0 mm, 71 parts (15 on the bottom side), 45 nets.

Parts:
AIN_REF0: NOT ASSEMBLED; 1PIN_1ROW_THT
C1, C2: 0603/4.7µF/10V; RCL_0603
C3: 0603/10nF/10V; RCL_0603
C5, C7, C10, C15: C0603/100nF/50V; C0603
C6: C0603/4µ7/16V; C0603
C8: C0603/22nF/50V; C0603
C9: C0603/470nF/16V; C0603
C11: 1210/4.7uF/100V; C1210
C12, C13: EEUFR1J151 150uF/63V/0R045; C_POL_RAD_THT_5X10X12.5
C14: 0805/4µ7/50V; C0805
C_ID0: C_ID/10V/1%; RCL_0603
D1: SMBJ43A; SMB
D3, D4: BAT54S; SOT23
IC1: SN74LVC1G123DCTR
IC2: LP2985AIM5-3.3; SOT23-5
INTERFACE_TO_UC/MC0: FEMALE_HEADER_SMD_254_44_PIN_SHORTPADS_HOLES
JMP1: JUMPER_2.54MM BLACK ON X2; EXTRA_TERMINAL
JMP2: JUMPER_2.54MM BLACK ON X1; EXTRA_TERMINAL
MOTOR1: AKL182_04_POL_HEADER; AKL169_04_POL
PROBE_GND0, PROBE_GND1, PROBE_GND2, PROBE_GND3: NOT ASSEMBLED; 1PIN_1ROW_THT
PWR0: AKL_349_02_POL_HEADER; AKL349_02_POL
R1: 0603/10k/1%; RCL_0603
R2: 10K; RCL_0603
R5, R7: R1206,0R22/0.5W; R1206
R6: 0603/2R2/1%; R0603
R8: NOT ASSEMBLED; R0603
R9: 0603/0R; R0603
R10: 10k/0603/1%; RCL_0603
R11: 15k/0603/1%; RCL_0603
R12, R13: 0603/10k/1%; 0603
R14, R15: 0603/1k/1%; 0603
R17: 4k7/0603/1%; RCL_0603
REF2: MALE HEADER 2.54; 3PIN_1ROW_2,54_THT
RSENSE_A0: NOT ASSEMBLED; 1PIN_1ROW_THT
RSENSE_B0: NOT ASSEMBLED; 1PIN_1ROW_THT
R_ID0: R_ID/1%; RCL_0603
R_SD0: NOT_ASSEMBLED; RCL_0603
R_SPI0: NOT_ASSEMBLED; RCL_0603
TERM1: AKL_330_2_POL_TERMINAL; EXTRA_TERMINAL
TERM2: AKL182_04_POL_TERMINAL; EXTRA_TERMINAL
TEST_POINT1, TEST_POINT2, TEST_POINT3, TEST_POINT4, TEST_POINT5, TEST_POINT6, TEST_POINT7, TEST_POINT8, TEST_POINT9, TEST_POINT10, TEST_POINT11, TEST_POINT12, TEST_POINT13, TEST_POINT14: NOT ASSEMBLED; PAD_R1.2
TMC2130: TMC2130_QFN36; QFN36
U$1: TMC_EVAL_RIGHT_BAR
U$3: TMC_EVAL_BACK_NO_DOCU
X1, X2: MALE HEADER 2.54; 3PIN_1ROW_2,54_THT

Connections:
+3V3: C2.1, IC1.8, IC2.5, R2.1, R9.1, R_ID0.2, TEST_POINT1.P$1
+5V_USB: C1.1, IC2.1, IC2.3, INTERFACE_TO_UC/MC0.5, R8.2
AIN_REF: AIN_REF0.1, R10.2, R11.2, TMC2130.23
AIN_REF_PWM: INTERFACE_TO_UC/MC0.22, R17.1
AIN_REF_SW: INTERFACE_TO_UC/MC0.21, R11.1
CLK: INTERFACE_TO_UC/MC0.23, TMC2130.1
CSN_CFG3: INTERFACE_TO_UC/MC0.24, TMC2130.2
DRV_ENN_CFG6: INTERFACE_TO_UC/MC0.8, TMC2130.22
ENCA_DCIN_CFG5: INTERFACE_TO_UC/MC0.34, TMC2130.19
ENCB_DCEN_CFG4: INTERFACE_TO_UC/MC0.35, TMC2130.18
ENCN_DCO: INTERFACE_TO_UC/MC0.36, TMC2130.17
EXT_DIR: D3.3, R14.2, X2.1
EXT_DIR_CON: R12.2, R14.1, REF2.1
EXT_STEP: D4.3, R15.2, X1.1
EXT_STEP_CON: R13.2, R15.1, REF2.2
GND: C1.2, C2.2, C3.2, C5.2, C6.2, C9.1, C10.1, C11.2, C12.-, C13.-, C14.1, C15.1, C_ID0.2, D1.A, D3.1, D4.1, IC1.1, IC1.4, IC1.6, IC2.2, INTERFACE_TO_UC/MC0.2, INTERFACE_TO_UC/MC0.3, INTERFACE_TO_UC/MC0.43, INTERFACE_TO_UC/MC0.44, PROBE_GND0.1, PROBE_GND1.1, PROBE_GND2.1, PROBE_GND3.1, PWR0.1, R1.2, R5.1, R7.1, R12.1, R13.1, REF2.3, R_SD0.1, R_SPI0.1, TEST_POINT14.P$1, TMC2130.11, TMC2130.12, TMC2130.24, TMC2130.35, TMC2130.36, TMC2130.GND_PAD
ID_CH1: IC1.5, INTERFACE_TO_UC/MC0.7
ID_CLK: IC1.2, INTERFACE_TO_UC/MC0.4, R1.1
INT_DIR: INTERFACE_TO_UC/MC0.18, X2.3
INT_STEP: INTERFACE_TO_UC/MC0.17, X1.3
M1A: MOTOR1.3, TMC2130.34
M1A2: MOTOR1.4, TMC2130.32
M1B1: MOTOR1.1, TMC2130.13
M1B2: MOTOR1.2, TMC2130.15
unnamed: C3.1, IC1.3, R2.2
unnamed: C_ID0.1, IC1.7, R_ID0.1
unnamed: R_SPI0.2, TMC2130.10
unnamed: R_SD0.2, TMC2130.9
unnamed: C6.1, R6.1, TMC2130.25
unnamed: C8.1, TMC2130.28
unnamed: C8.2, TMC2130.27
unnamed: C7.2, TMC2130.29
unnamed: C9.2, R6.2, TMC2130.26
unnamed: C14.2, R10.1, R17.2
SCK_CFG2: INTERFACE_TO_UC/MC0.27, TMC2130.3
SDI_NAI_CFG1: INTERFACE_TO_UC/MC0.29, TMC2130.4
SDO_NAO_CFG0: INTERFACE_TO_UC/MC0.28, TMC2130.5
SENSEA: R5.2, RSENSE_A0.1, TEST_POINT2.P$1, TMC2130.33
SENSEB: R7.2, RSENSE_B0.1, TEST_POINT3.P$1, TMC2130.14
SEP_DIAG1: INTERFACE_TO_UC/MC0.38, TMC2130.21
SWN_DIAG0: INTERFACE_TO_UC/MC0.37, TMC2130.20
VCC_IO: C5.1, D3.2, D4.2, R8.1, R9.2, TMC2130.8
VM: C7.1, C10.2, C11.1, C12.+, C13.+, C15.2, D1.C, INTERFACE_TO_UC/MC0.1, PWR0.2, TMC2130.16, TMC2130.30, TMC2130.31
[REFL]_STEP: TMC2130.6, X1.2
[REFR]_DIR: TMC2130.7, X2.2
